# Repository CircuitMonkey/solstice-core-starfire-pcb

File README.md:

# solstice-core-starfire-pcb
Solstice Design System —  *Starfire* Core —  Eagle PCB

PCB files for the **Circuit Monkey** *StarFire*  **Solstice Core** *Module*

Format is EagleCAD 9.x schematic and board layout

*StarFire* is one of the first *Solstice Core* modules.

For more details, check out the product page at

  * https://www.circuitmonkey.com/product/0701   ( [404 - not found] this link is not yet active)

### Revision Notes
* Rev. 0 - Initial board design.  This revision was made for evaluation and only
one unit ever made.

* Rev. A - First revision meant for human consumption.
  * Swapped Vin and GND pins on HaLo connector.   Vin was dangerously close to GND mounting hole.
  * Changed WS2812B (5x5mm) LEDs to smaller SK6812(3.5x3.5mm LEDs)
  * SK6812 LED chain is driven by SCK pin.  Was MISO pin on Rev.0 and pattern would scramble when ISP programming the board.
  * Reset switch changed to slightly larger type.
  * Mounting holes on corners changed from 2mm pan head-style to 3mm socket head type.  2mm hardware is harder to source.
  * Added Umbra connector.  A Umbra is 20-pin micro-shield that is approx. 1x1 inch and can mount under the regular shield(HaLo).
  * Added Umbra hardware mounting points throughout PCB.
  * Added mounting holes to support light pipe option at the PWR and D13 LEDs.

* Rev. B - Production version.
  * Added EN_PIXELS solder jumper on bottom of PCB to allow disabling of built-in RGB LEDs.
  * Added test points at bottom of PCB to allow externally extending the 16 on-board LEDs.
  * Added 330ohm serial resistor to external pixel output.
  * USB connector footprint issue addressed.  Footprint was correct, Seeed part number was incorrect.

## Designed by Circuit Monkey in Las Vegas, Nevada, USA
Creative Commons Attribution, Share-Alike license, check license.txt for more information. Derivative of "Arduino Leonardo Reference design" (http://www.arduino.cc/en/Main/ArduinoBoardLeonardo)

All text above must be included in any redistribution

## Gallery

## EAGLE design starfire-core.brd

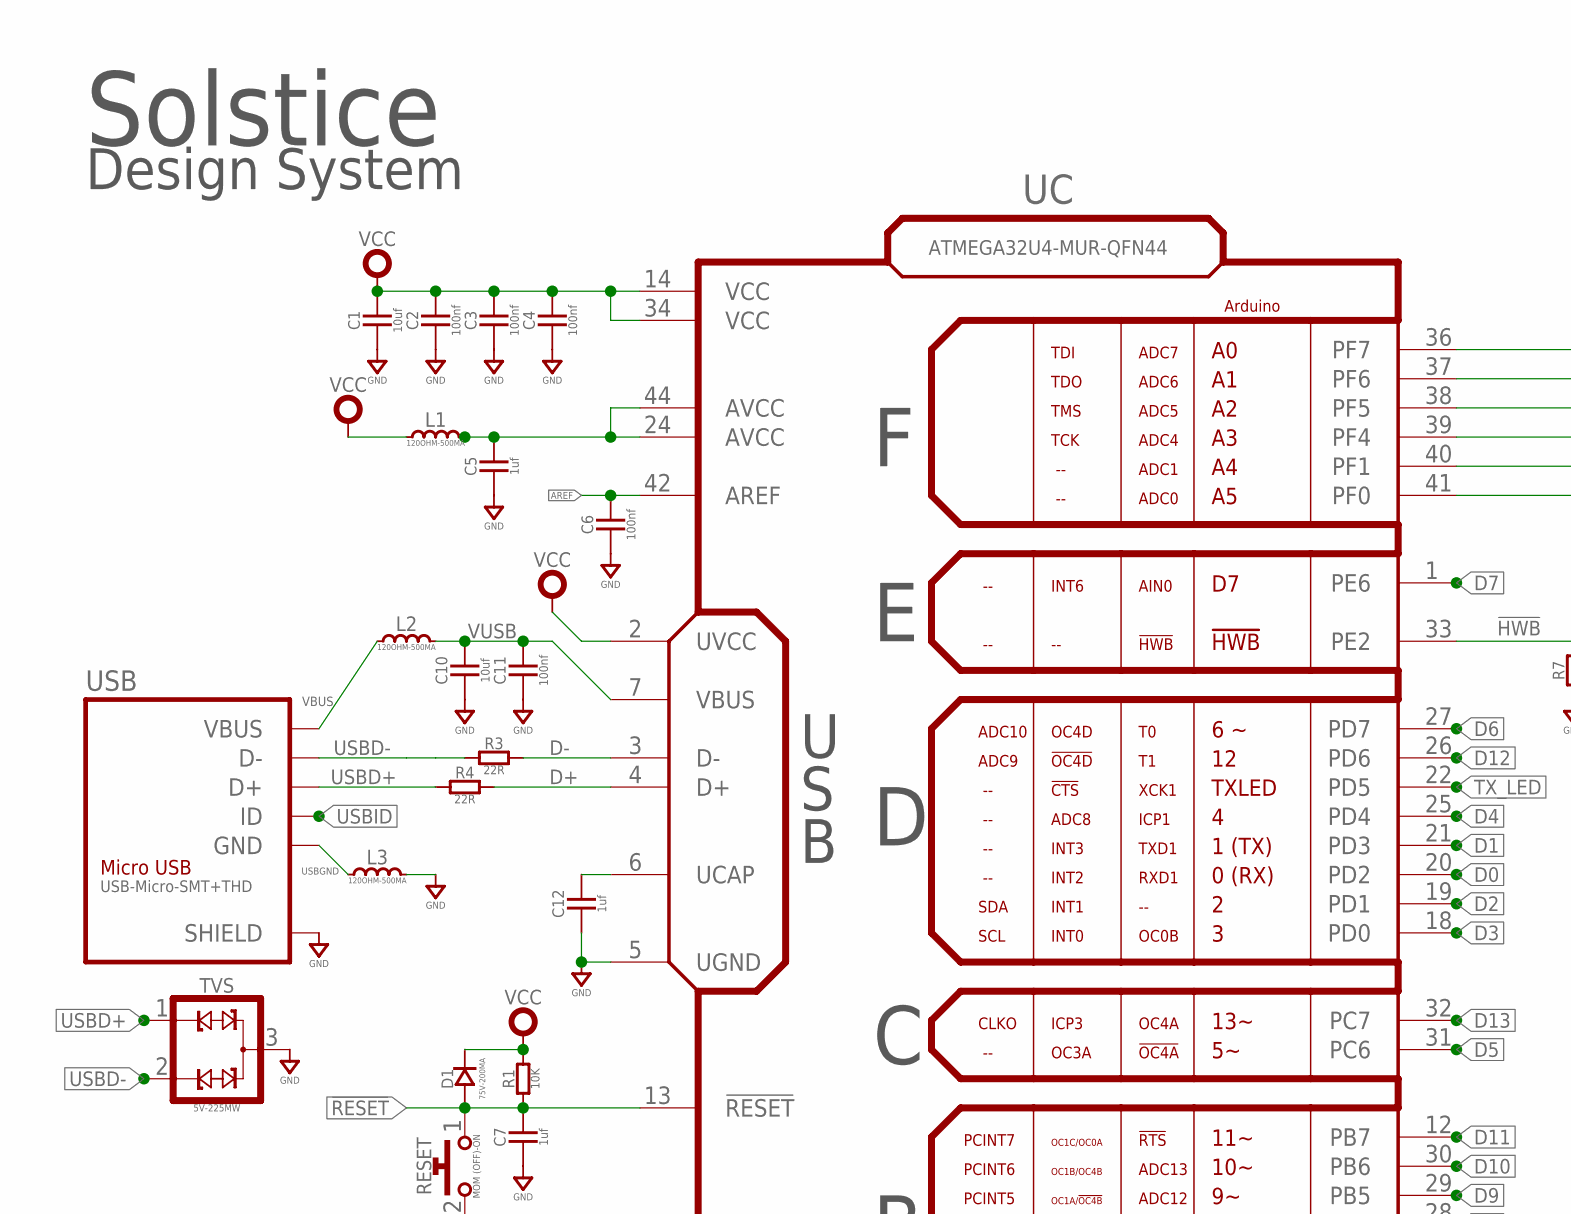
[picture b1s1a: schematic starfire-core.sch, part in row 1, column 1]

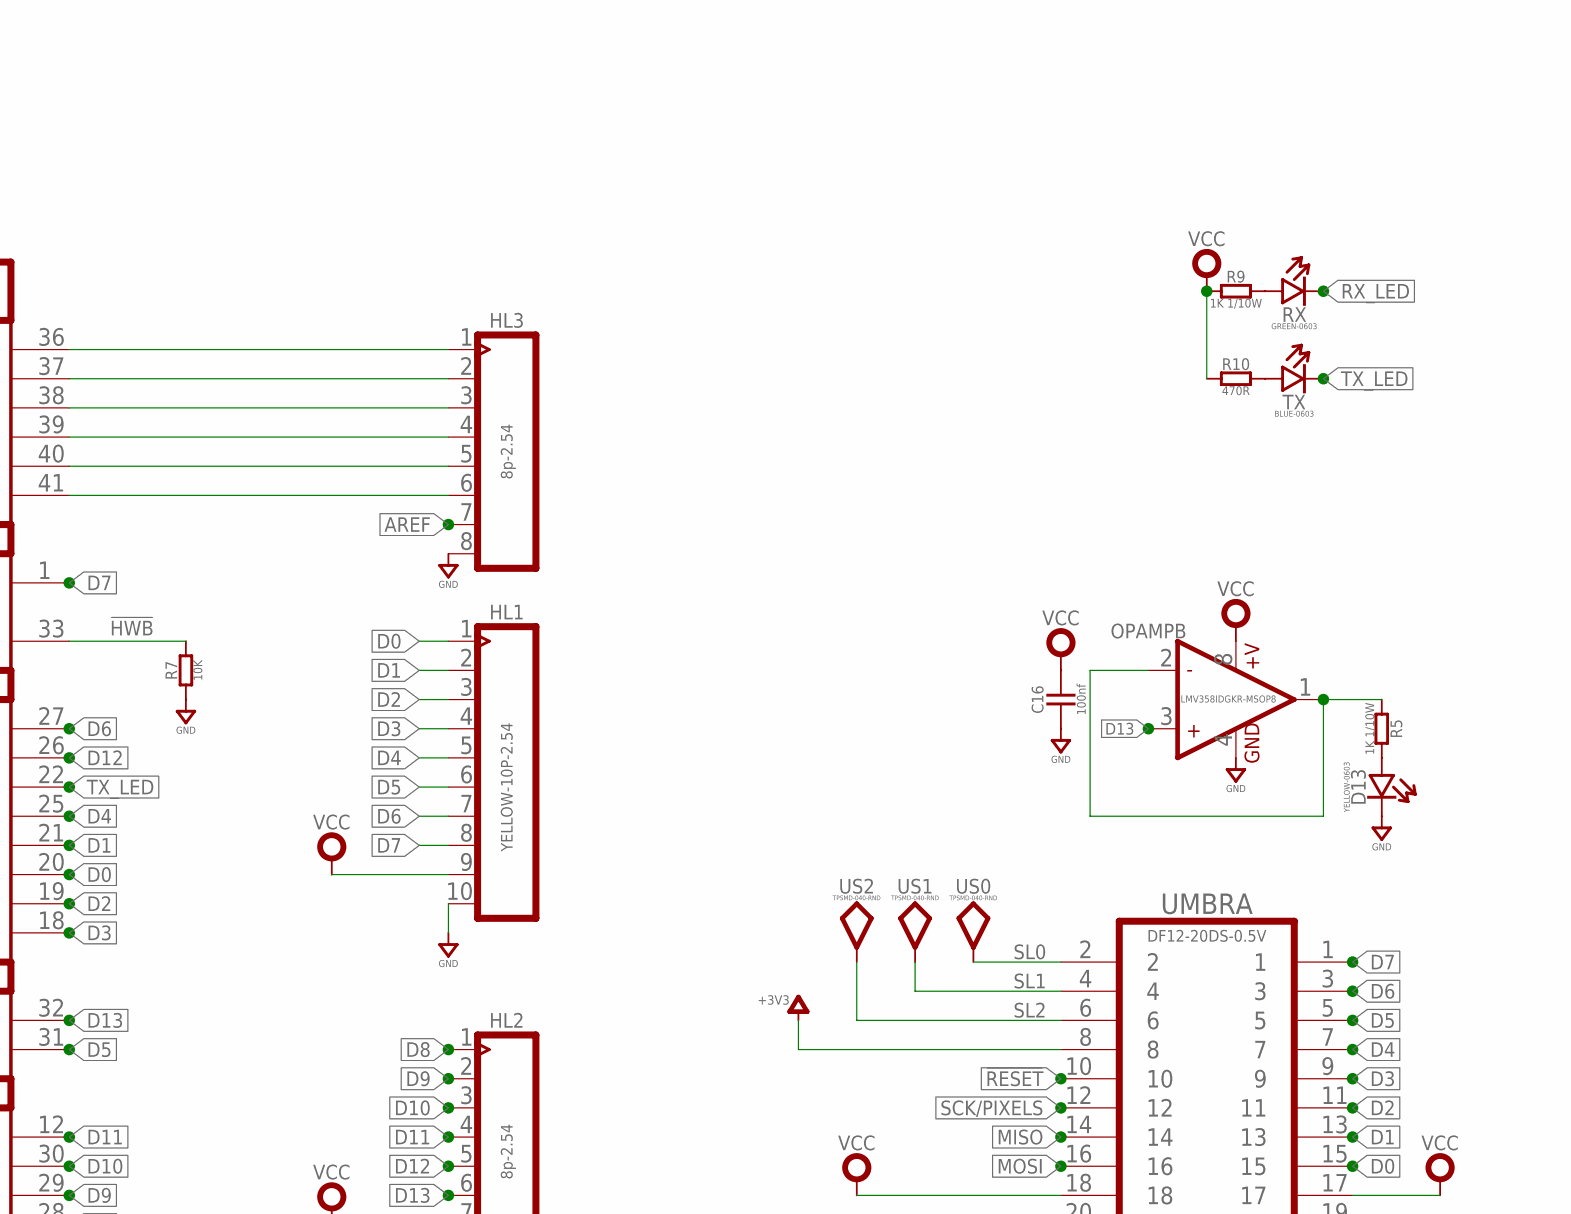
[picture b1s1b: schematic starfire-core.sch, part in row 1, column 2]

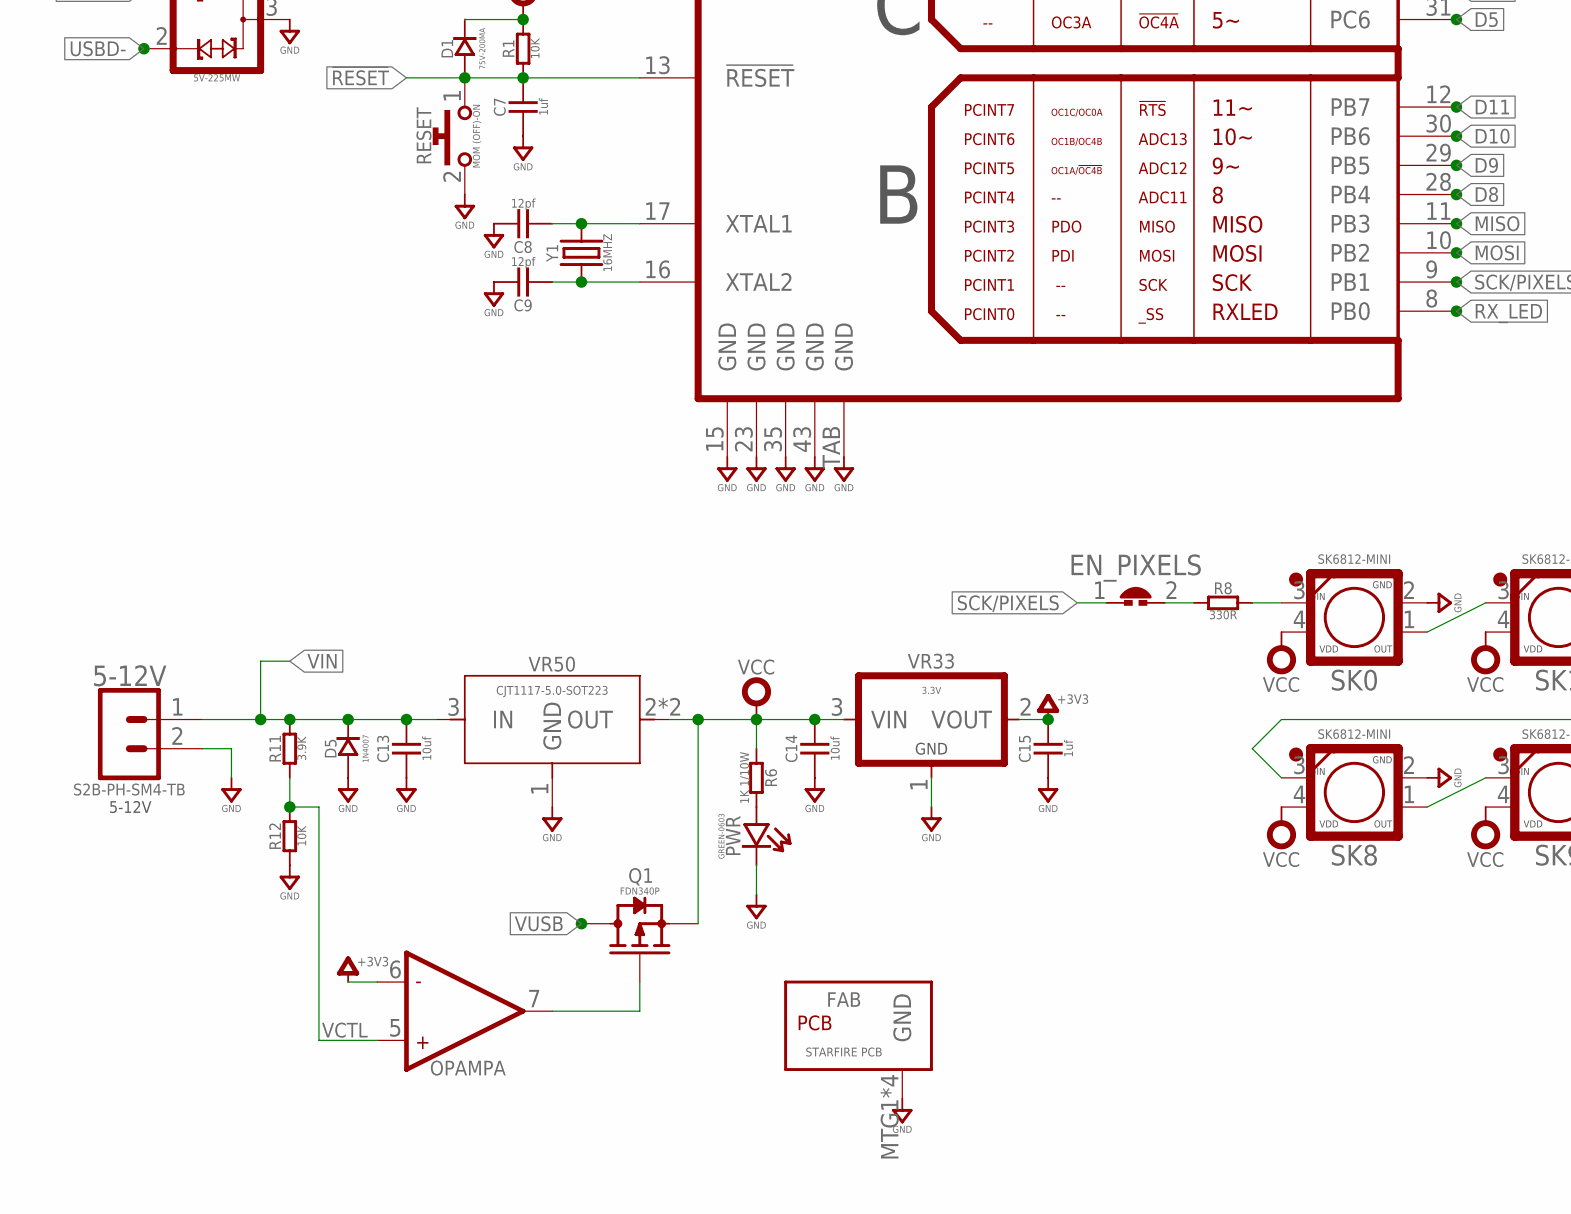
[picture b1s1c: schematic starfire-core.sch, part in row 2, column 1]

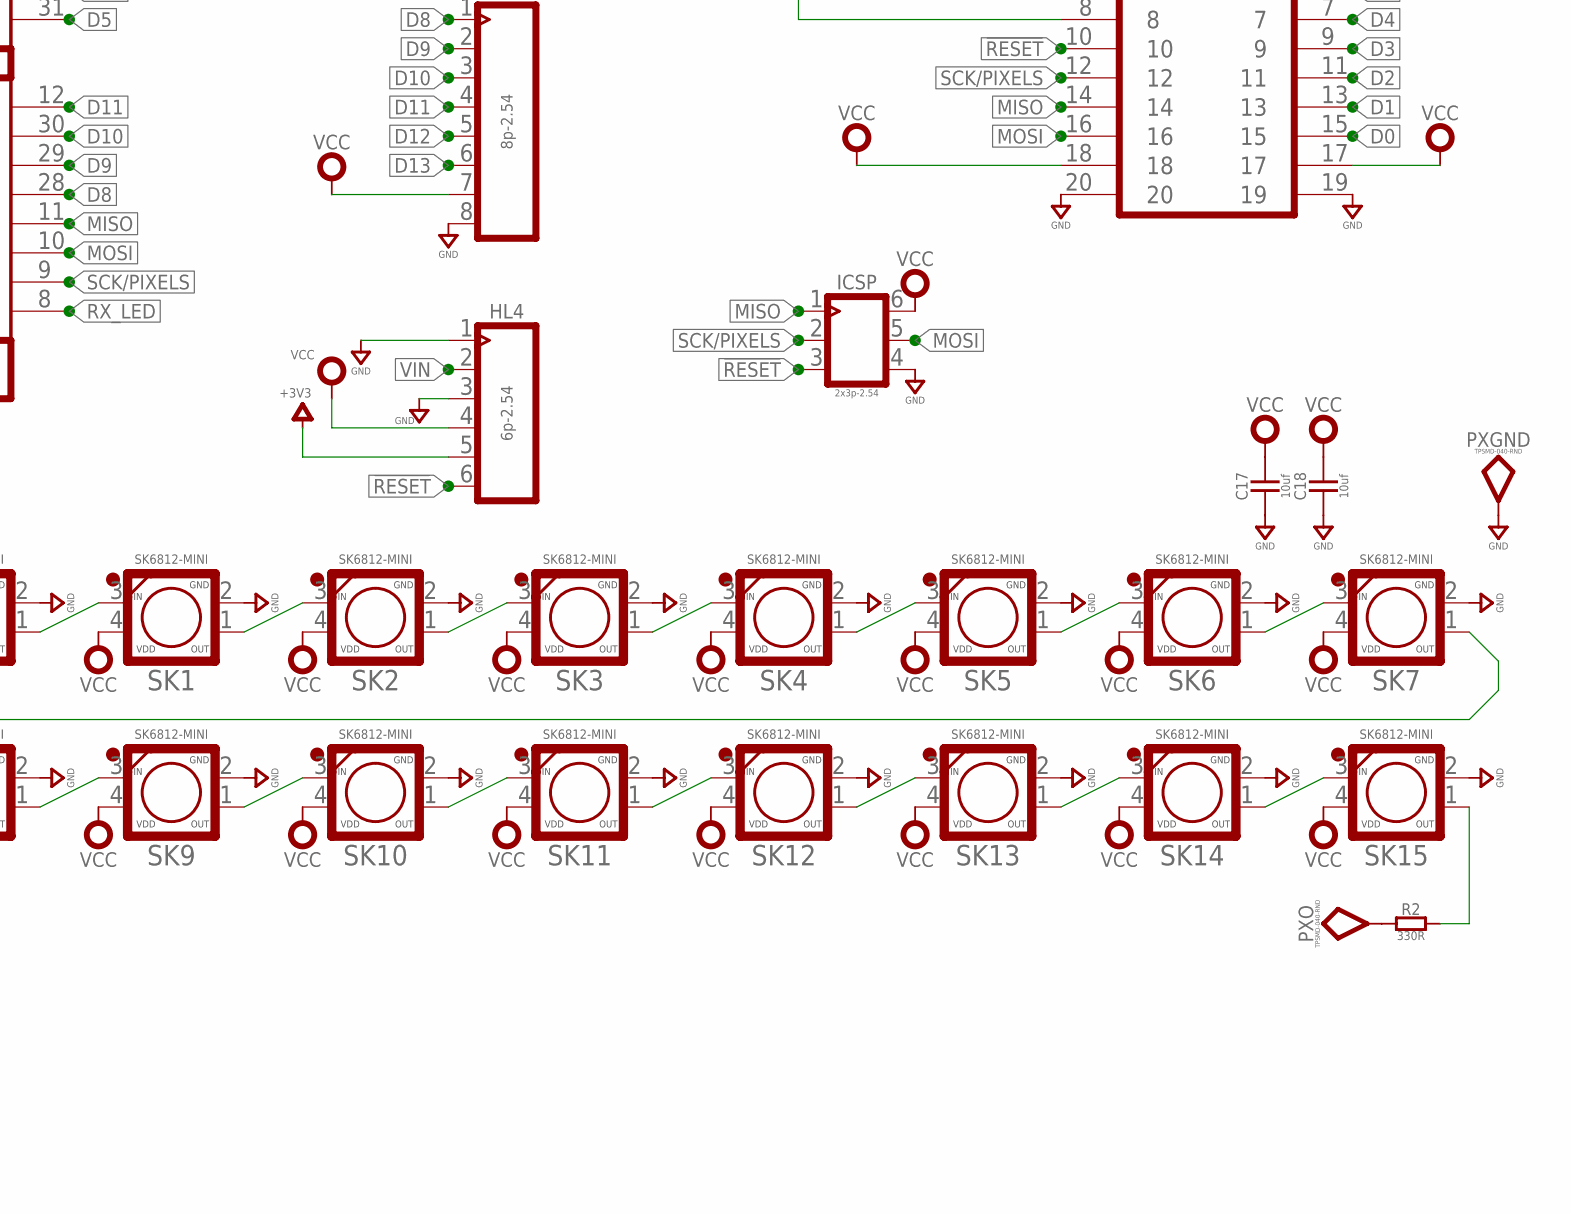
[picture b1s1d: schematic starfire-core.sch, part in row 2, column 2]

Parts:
5-12V: S2B-PH-SM4-TB; S2B-PH-SM4-
C1, C10, C13, C14, C17, C18: 10uf; C0603
C2, C3, C4, C6, C11, C16: 100nf; C0603
C5, C7, C12, C15: 1uf; C0603
C8, C9: 12pf; C0603
D1: 75V-200MA; LL-34
D5: 1N4007; DO-214AC
D13: YELLOW-0603; LED-0603
EN_PIXELS: SOLDER_JUMPER-80MIL-RND; SOLDER_JUMP_80MIL_RND
FAB: STARFIRE PCB; PCB-BASE-B1
HL1: YELLOW-10P-2.54; H10-2.54
HL2, HL3: 8p-2.54; H8-2.54
HL4: 6p-2.54; H6-2.54
ICSP: 2x3p-2.54; H2X3-2.54
L1, L2, L3: 120OHM-500MA; L0603
OPAMP: LMV358IDGKR-MSOP8; MSOP8-0.65-3X3MM
PWR: GREEN-0603; LED-0603
PXGND: TPSMD-040-RND; SMD-040MIL-RND
PXO: TPSMD-040-RND; SMD-040MIL-RND
Q1: FDN340P; SOT-23
R1, R7, R12: 10K; R0603
R2, R8: 330R; R0603
R3, R4: 22R; R0603
R5, R6, R9: 1K 1/10W; R0603
R10: 470R; R0603
R11: 3.9K; R0603
RESET: MOM (OFF)-ON; SWITCH-0635-2P-SMD
RX: GREEN-0603; LED-0603
SK0, SK1, SK2, SK3, SK4, SK5, SK6, SK7, SK8, SK9, SK10, SK11, SK12, SK13, SK14, SK15: SK6812-MINI; SMD_3535
TVS: 5V-225MW; SOT-23
TX: BLUE-0603; LED-0603
UC: ATMEGA32U4-MUR-QFN44; QFN44G-0.5-7X7MM
UMBRA: DF12-20DS-0.5V; DF12-20P-RCPT-MTL-BOSS
US0, US1, US2: TPSMD-040-RND; SMD-040MIL-RND
USB: USB-Micro-SMT+THD; MICRO-USB5+6P-SMD-0.65-AB
VR33: 3.3V; SOT-23
VR50: CJT1117-5.0-SOT223; SOT-223
Y1: 16MHZ; X2-SMD-5.0X3.2X1.3MM

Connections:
!HWB: R7.2, UC.33 (PE2)
!RESET: C7.2, D1.A (+), HL4.6, ICSP.3, R1.1, RESET.1, UC.13 (!RESET), UMBRA.10
+3V3: C15.2, HL4.5, OPAMP.6 (-IN2), UMBRA.8, VR33.2 (VOUT)
AREF: C6.2, HL3.7, UC.42 (AREF)
AVCC: C5.2, L1.2, UC.24 (AVCC), UC.44 (AVCC)
D0: HL1.1, UC.20 (PD2), UMBRA.15
D1: HL1.2, UC.21 (PD3), UMBRA.13
D2: HL1.3, UC.19 (PD1), UMBRA.11
D3: HL1.4, UC.18 (PD0), UMBRA.9
D4: HL1.5, UC.25 (PD4), UMBRA.7
D5: HL1.6, UC.31 (PC6), UMBRA.5
D6: HL1.7, UC.27 (PD7), UMBRA.3
D7: HL1.8, UC.1 (PE6), UMBRA.1
D8: HL2.1, UC.28 (PB4)
D9: HL2.2, UC.29 (PB5)
D10: HL2.3, UC.30 (PB6)
D11: HL2.4, UC.12 (PB7)
D12: HL2.5, UC.26 (PD6)
D13: HL2.6, OPAMP.3 (+IN1), UC.32 (PC7)
D+: R4.2, UC.4 (D+)
D-: R3.2, UC.3 (D-)
GND: 5-12V.2, C1.1, C2.1, C3.1, C4.1, C5.1, C6.1, C7.1, C8.2, C9.2, C10.1, C11.1, C12.1, C13.1, C14.1, C15.1, C16.1, C17.1, C18.1, D5.1 (+), D13.-, FAB.MTG1, FAB.MTG2, FAB.MTG3, FAB.MTG4, HL1.10, HL2.8, HL3.8, HL4.1, HL4.3, ICSP.4, L3.2, OPAMP.4 (GND), PWR.-, PXGND.TP, R7.1, R12.1, RESET.2, SK0.2 (GND), SK1.2 (GND), SK2.2 (GND), SK3.2 (GND), SK4.2 (GND), SK5.2 (GND), SK6.2 (GND), SK7.2 (GND), SK8.2 (GND), SK9.2 (GND), SK10.2 (GND), SK11.2 (GND), SK12.2 (GND), SK13.2 (GND), SK14.2 (GND), SK15.2 (GND), TVS.3, UC.5 (UGND), UC.15 (GND), UC.23 (GND), UC.35 (GND), UC.43 (GND), UC.TAB (GND), UMBRA.19, UMBRA.20, USB.P1 (SHIELD), USB.P2 (SHIELD), USB.P3_1 (SHIELD), USB.P3_2 (SHIELD), USB.P3_3 (SHIELD), USB.P4_1 (SHIELD), USB.P4_2 (SHIELD), USB.P4_3 (SHIELD), USB.P5 (SHIELD), USB.P6 (SHIELD), VR33.1 (VSS), VR50.1 (GND)
MISO: ICSP.1, UC.11 (PB3), UMBRA.14
MOSI: ICSP.5, UC.10 (PB2), UMBRA.16
unnamed: SK0.1 (OUT), SK1.3 (IN)
unnamed: C8.1, UC.17 (XTAL1), Y1.2
unnamed: C9.1, UC.16 (XTAL2), Y1.1
unnamed: SK1.1 (OUT), SK2.3 (IN)
unnamed: SK2.1 (OUT), SK3.3 (IN)
unnamed: SK3.1 (OUT), SK4.3 (IN)
unnamed: HL3.1, UC.36 (PF7)
unnamed: D13.+, R5.2
unnamed: SK4.1 (OUT), SK5.3 (IN)
unnamed: PWR.+, R6.2
unnamed: SK5.1 (OUT), SK6.3 (IN)
unnamed: SK6.1 (OUT), SK7.3 (IN)
unnamed: SK8.1 (OUT), SK9.3 (IN)
unnamed: R8.2, SK0.3 (IN)
unnamed: SK9.1 (OUT), SK10.3 (IN)
unnamed: SK10.1 (OUT), SK11.3 (IN)
unnamed: SK11.1 (OUT), SK12.3 (IN)
unnamed: SK12.1 (OUT), SK13.3 (IN)
unnamed: SK13.1 (OUT), SK14.3 (IN)
unnamed: SK14.1 (OUT), SK15.3 (IN)
unnamed: R10.2, TX.+
unnamed: R9.2, RX.+
unnamed: HL3.2, UC.37 (PF6)
unnamed: HL3.3, UC.38 (PF5)
unnamed: HL3.4, UC.39 (PF4)
unnamed: HL3.5, UC.40 (PF1)
unnamed: HL3.6, UC.41 (PF0)
unnamed: SK7.1 (OUT), SK8.3 (IN)
unnamed: PXO.TP, R2.1
unnamed: R2.2, SK15.1 (OUT)
unnamed: OPAMP.1 (OUT1), OPAMP.2 (-IN1), R5.1
unnamed: OPAMP.7 (OUT2), Q1.1 (G)
PIXELS: EN_PIXELS.2, R8.1
RX_LED: RX.-, UC.8 (PB0)
SCK/PIXELS: EN_PIXELS.1, ICSP.2, UC.9 (PB1), UMBRA.12
SL0: UMBRA.2, US0.TP
SL1: UMBRA.4, US1.TP
SL2: UMBRA.6, US2.TP
TX_LED: TX.-, UC.22 (PD5)
UCAP: C12.2, UC.6 (UCAP)
USBD+: R4.1, TVS.1, USB.3 (D+)
USBD-: R3.1, TVS.2, USB.2 (D-)
USBGND: L3.1, USB.5 (GND)
USBID: USB.4 (ID)
VBUS: L2.1, USB.1 (VBUS)
VCC: C1.2, C2.2, C3.2, C4.2, C14.2, C16.2, C17.2, C18.2, D1.C (-), HL1.9, HL2.7, HL4.4, ICSP.6, L1.1, OPAMP.8 (+V), Q1.2 (S), R1.2, R6.1, R9.1, R10.1, SK0.4 (VDD), SK1.4 (VDD), SK2.4 (VDD), SK3.4 (VDD), SK4.4 (VDD), SK5.4 (VDD), SK6.4 (VDD), SK7.4 (VDD), SK8.4 (VDD), SK9.4 (VDD), SK10.4 (VDD), SK11.4 (VDD), SK12.4 (VDD), SK13.4 (VDD), SK14.4 (VDD), SK15.4 (VDD), UC.2 (UVCC), UC.14 (VCC), UC.34 (VCC), UMBRA.17, UMBRA.18, VR33.3 (VIN), VR50.2 (OUT), VR50.TER (OUT)
VCTL: OPAMP.5 (+IN2), R11.1, R12.2
VIN: 5-12V.1, C13.2, D5.2 (-), HL4.2, R11.2, VR50.3 (IN)
VUSB: C10.2, C11.2, L2.2, Q1.3 (D), UC.7 (VBUS)

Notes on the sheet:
Solstice
5-12V
Design System

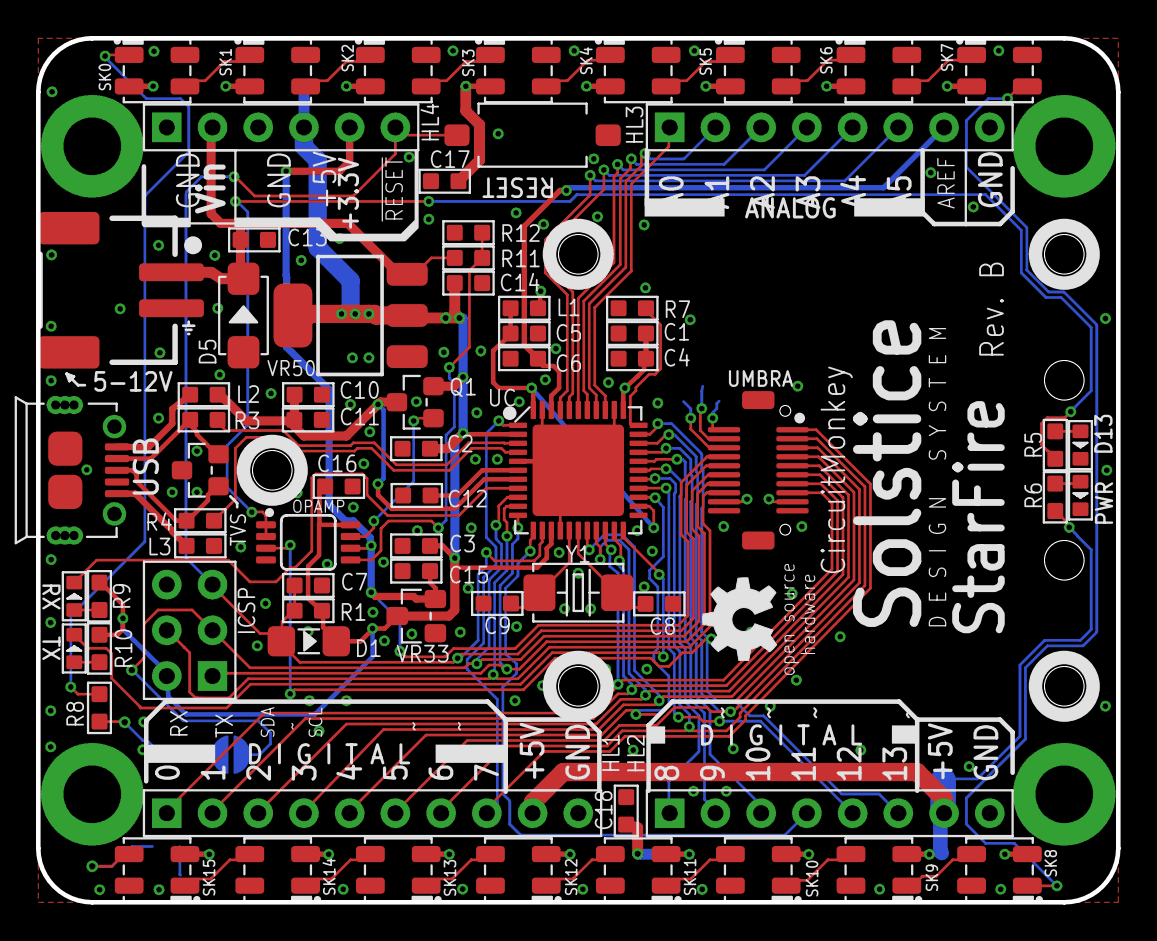
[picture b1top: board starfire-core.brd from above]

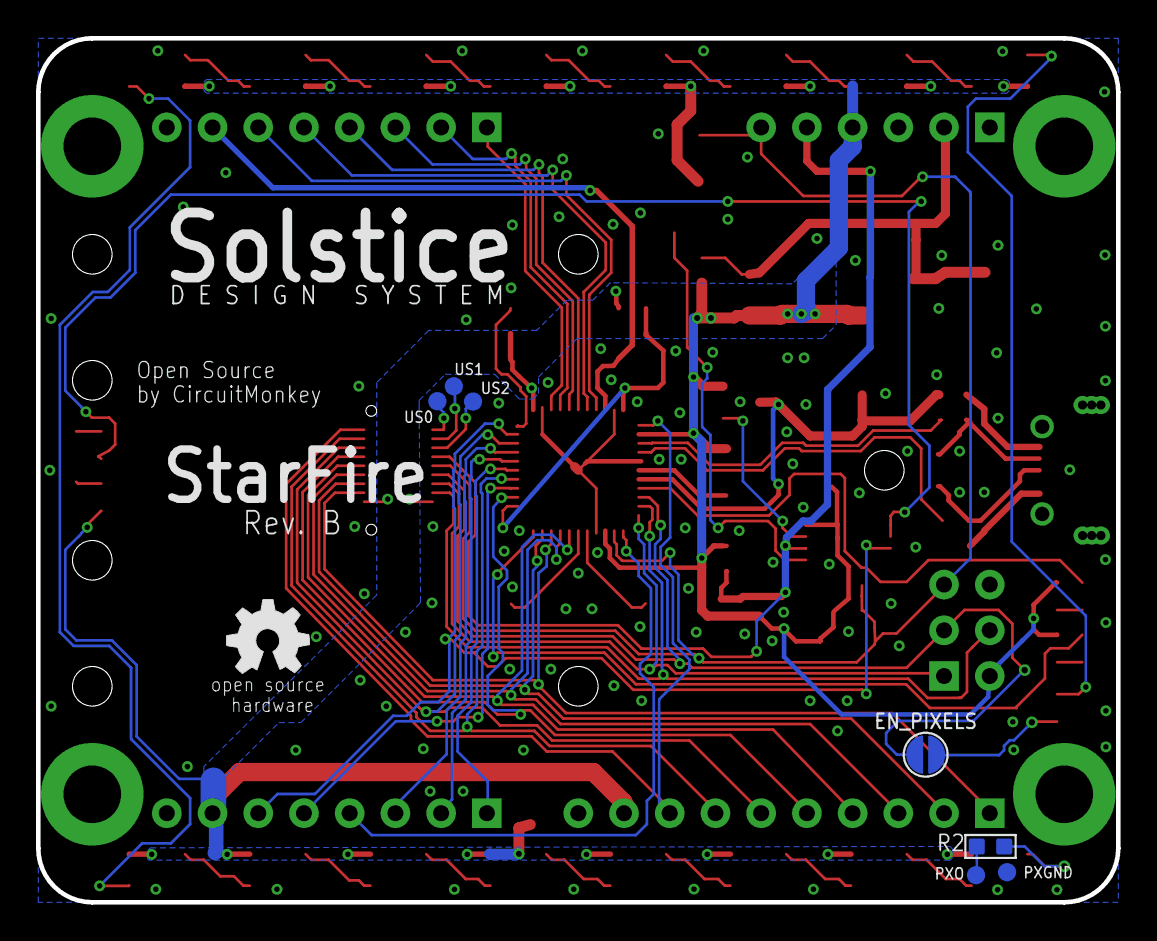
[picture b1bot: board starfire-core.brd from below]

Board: 2 copper layers, 60.0 x 48.0 mm, 80 parts (8 on the bottom side), 72 nets.

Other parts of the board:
U$2, U$3: OSHW_5MM

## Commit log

2018-05-11 Update title.
2018-05-20 Upload pre-release board proto BRD and SCH.
2018-06-10 starfire eaglecad lbr refernce moved.
    I renamed and moved the EagleCAD library for the PCB fab compoment to our public git repo. So updated the BRD and SCH references so that users can find the correct library.
2018-10-30 Rev. A PCBs shared to world
2018-10-30 CAD Image of PCB added
2018-10-30 Added image.
2018-10-30 Image links in MD files suck.
2018-10-30 Remove unwanted file
2018-12-02 Revision B released
    Added Umbra connector feature along with Umbra mount support holes. RGB LEDs are now smaller SK6812 type 3.5x3.5mm. Added output test points for external LED chain that extends on-board chain. Added 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
2018-12-02 New Images
2025-04-15 Added schematic PDF.
